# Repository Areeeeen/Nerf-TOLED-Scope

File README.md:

# Nerf-TOLED-Scope
A nerf rail attachment for a 1.51 inch transparent OLED based aiming scope.

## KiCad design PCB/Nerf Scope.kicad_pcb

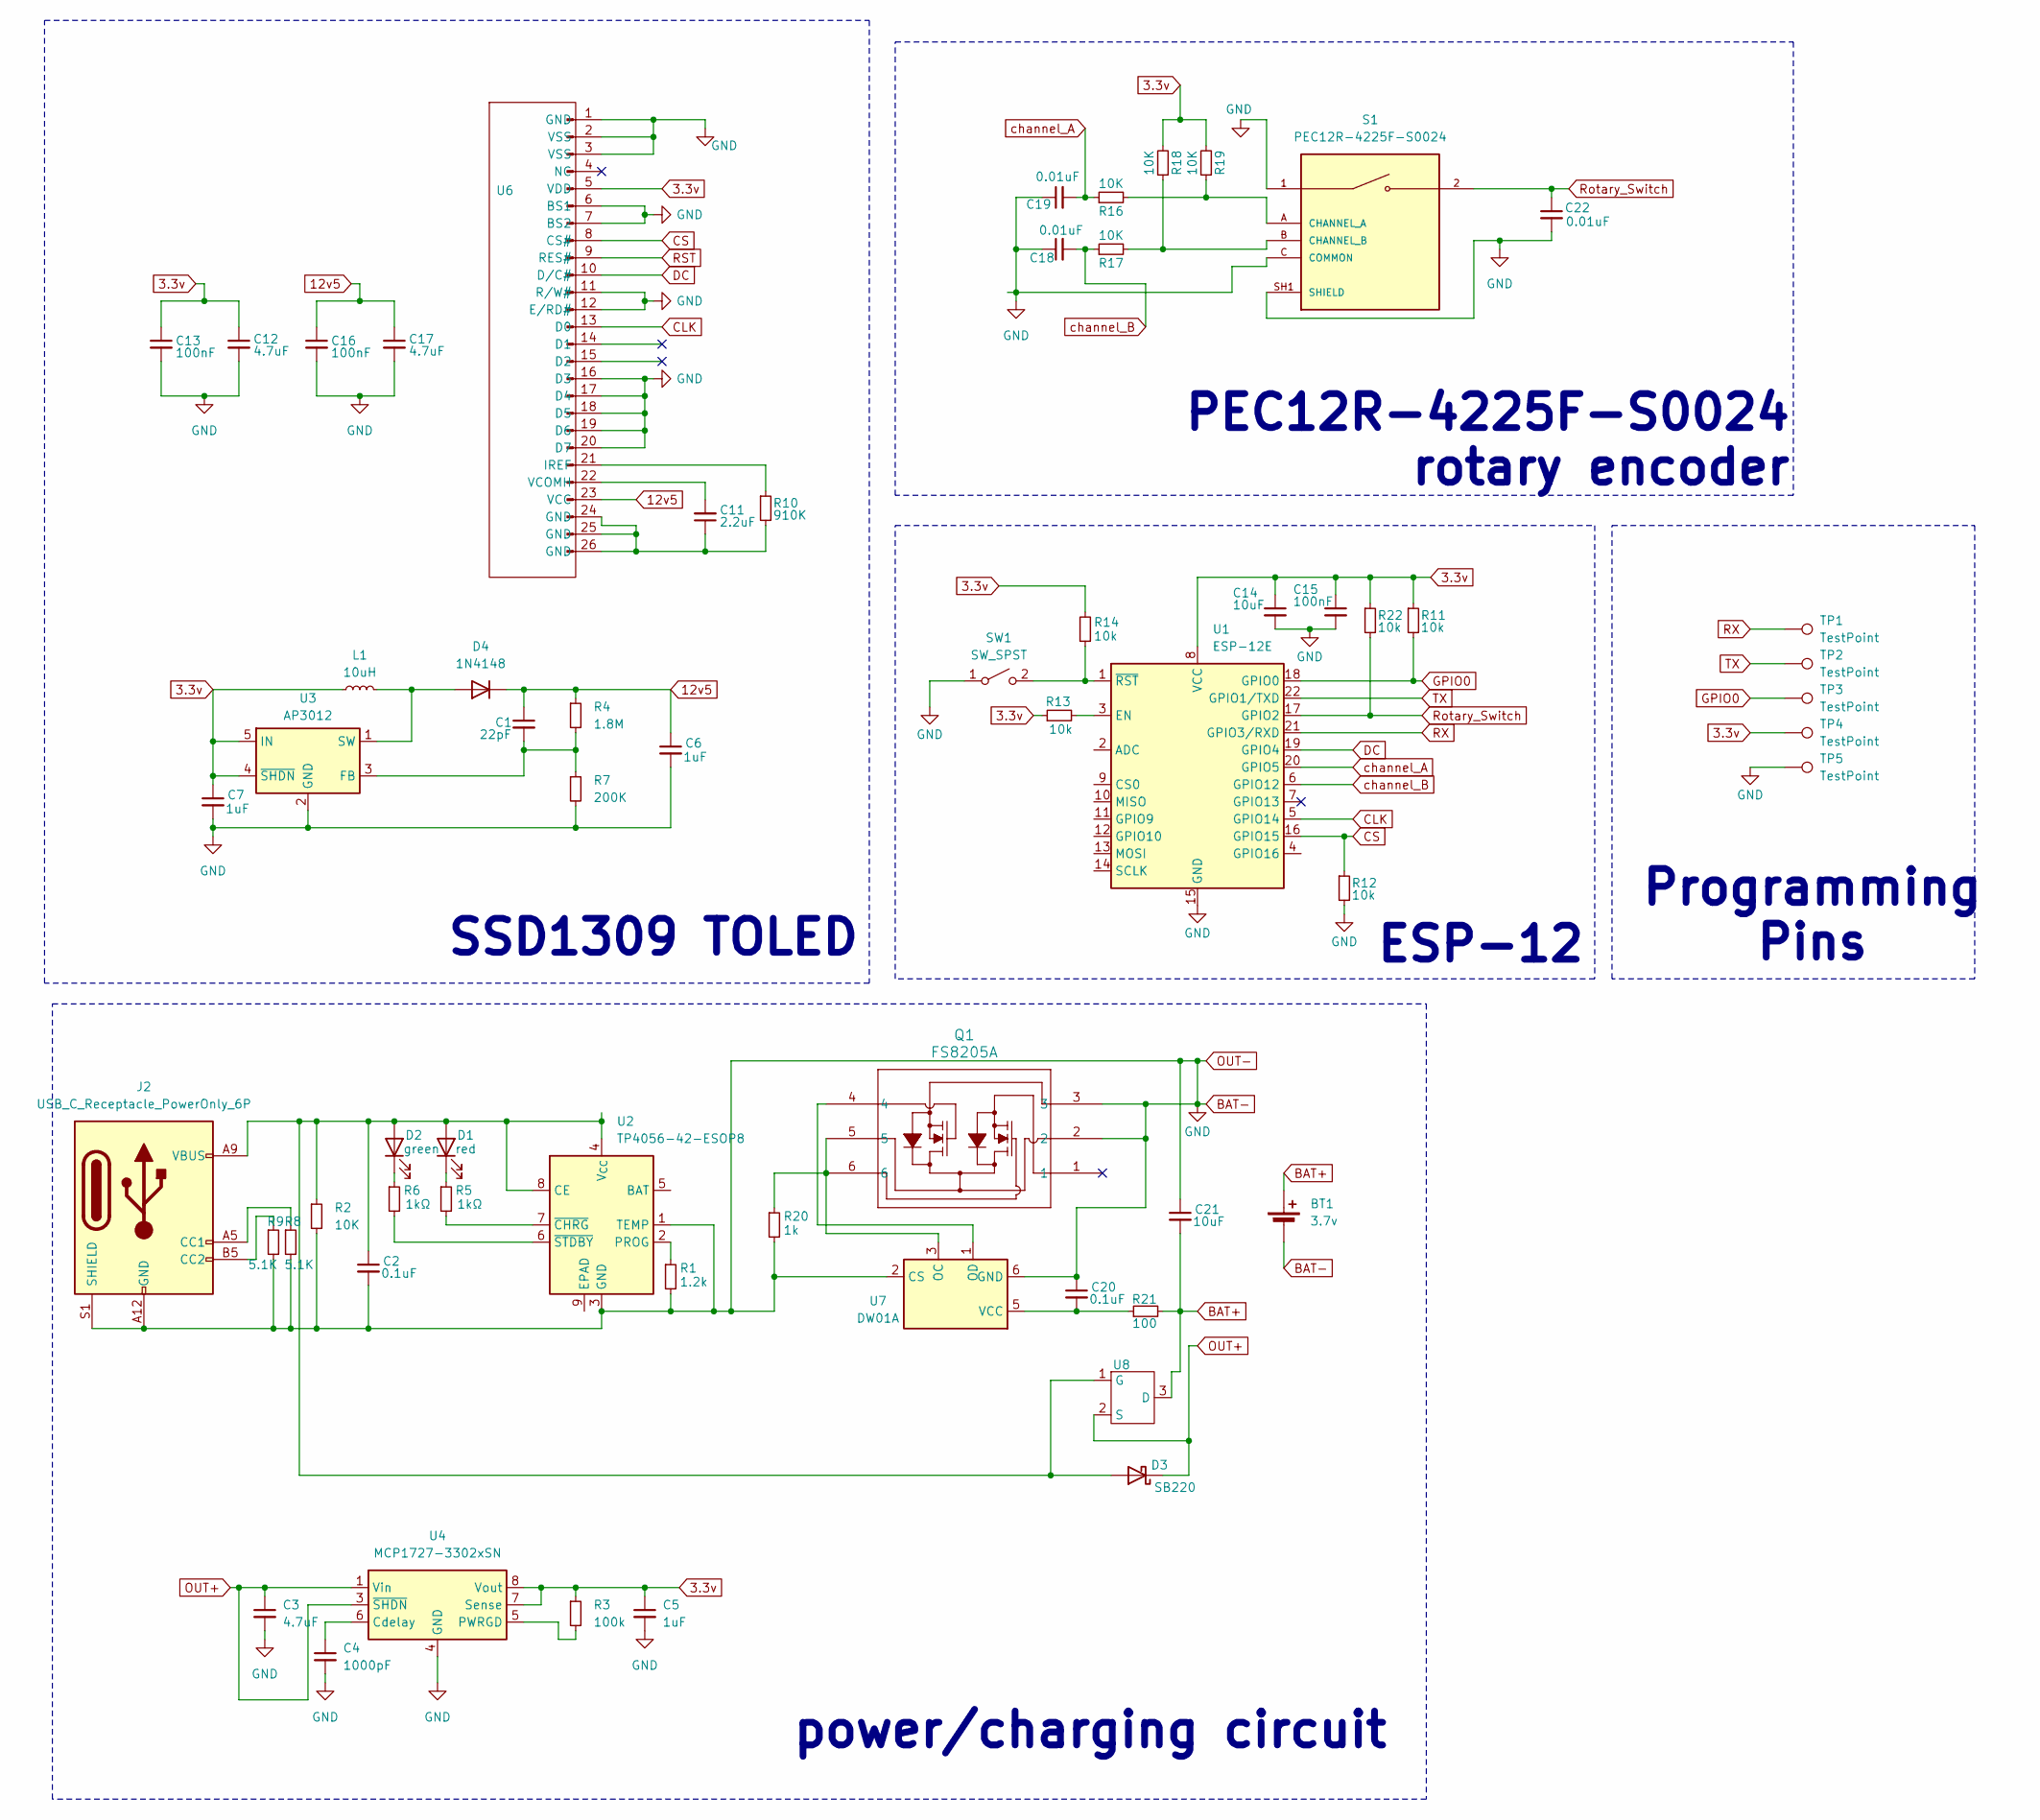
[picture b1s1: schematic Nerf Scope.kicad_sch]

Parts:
BT1: 3.7v; PinHeader_1x02_P2.54mm_Vertical
C1: 22pF; C_0603_1608Metric_Pad1.08x0.95mm_HandSolder
C2, C20: 0.1uF; C_0603_1608Metric_Pad1.08x0.95mm_HandSolder
C3, C12, C17: 4.7uF; C_0603_1608Metric_Pad1.08x0.95mm_HandSolder
C4: 1000pF; C_0603_1608Metric_Pad1.08x0.95mm_HandSolder
C5, C6, C7: 1uF; C_0603_1608Metric_Pad1.08x0.95mm_HandSolder
C11: 2.2uF; C_0603_1608Metric_Pad1.08x0.95mm_HandSolder
C13, C15, C16: 100nF; C_0603_1608Metric_Pad1.08x0.95mm_HandSolder
C14, C21: 10uF; C_0603_1608Metric_Pad1.08x0.95mm_HandSolder
C18, C19, C22: 0.01uF; C_0603_1608Metric_Pad1.08x0.95mm_HandSolder
D1: red; LED_0805_2012Metric_Pad1.15x1.40mm_HandSolder
D2: green; LED_0805_2012Metric_Pad1.15x1.40mm_HandSolder
D3: SB220; D_DO-15_P10.16mm_Horizontal
D4: 1N4148; D_DO-35_SOD27_P7.62mm_Horizontal
J2: USB_C_Receptacle_PowerOnly_6P; USB_C_Receptacle_GCT_USB4125-xx-x-0190_6P_TopMnt_Horizontal
L1: 10uH; Murata_45103C
Q1: FS8205A; SOT-23-6
R1: 1.2k; R_0603_1608Metric_Pad0.98x0.95mm_HandSolder
R2, R16, R17, R18, R19: 10K; R_0603_1608Metric_Pad0.98x0.95mm_HandSolder
R3: 100k; R_0603_1608Metric_Pad0.98x0.95mm_HandSolder
R4: 1.8M; R_0603_1608Metric_Pad0.98x0.95mm_HandSolder
R5, R6: 1kΩ; R_0603_1608Metric_Pad0.98x0.95mm_HandSolder
R7: 200K; R_0603_1608Metric_Pad0.98x0.95mm_HandSolder
R8, R9: 5.1K; R_0603_1608Metric_Pad0.98x0.95mm_HandSolder
R10: 910K; R_0603_1608Metric_Pad0.98x0.95mm_HandSolder
R11, R12, R13, R14, R22: 10k; R_0603_1608Metric_Pad0.98x0.95mm_HandSolder
R20: 1k; R_0603_1608Metric_Pad0.98x0.95mm_HandSolder
R21: 100; R_0603_1608Metric_Pad0.98x0.95mm_HandSolder
S1: PEC12R-4225F-S0024; PARTREV 07/21
SW1: SW_SPST; Untitled
TP1, TP2, TP3, TP4, TP5: TestPoint; Untitled_1
U1: ESP-12E
U2: TP4056-42-ESOP8; SOIC-8-1EP_3.9x4.9mm_P1.27mm_EP2.41x3.3mm_ThermalVias
U3: AP3012; SOT-23-5
U4: MCP1727-3302xSN; SOIC-8_3.9x4.9mm_P1.27mm
U6: Molex_502244-2430_1x24-1MP_P0.5mm_Horizontal
U7: DW01A; SOT-23-6
U8: SOT23-3_PO132

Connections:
3.3v: C5.1, C7.1, C12.1, C13.1, C14.1, C15.1, L1.1, R3.1, R11.1, R13.1, R14.2, R18.2, R19.2, R22.1, TP4.1, U1.8 (VCC), U3.4 (~SHDN), U3.5 (IN), U4.7 (Sense), U4.8 (Vout), U6.5 (VDD)
12v5: C1.1, C6.1, C16.1, C17.1, D4.1 (K), R4.1, U6.23 (VCC)
BAT+: BT1.1 (+), C21.2, R21.2, U8.3 (D)
BAT-: BT1.2 (-), C2.2, C3.2, C4.2, C5.2, C6.2, C7.2, C12.2, C13.2, C14.2, C15.2, C16.2, C17.2, C18.1, C19.1, C20.1, C21.1, C22.2, J2.A12 (GND), J2.B12 (GND), J2.S1 (SHIELD), Q1.2, Q1.3, R1.2, R2.2, R7.2, R8.2, R9.2, R12.2, R20.2, S1.1, S1.C (COMMON), S1.SH1 (SHIELD), S1.SH2 (SHIELD), SW1.1 (A), TP5.1, U1.15 (GND), U2.1 (TEMP), U2.3 (GND), U3.2 (GND), U4.4 (GND), U6.1 (GND), U6.2 (VSS), U6.3 (VSS), U6.6 (BS1), U6.7 (BS2), U6.11 (R/W#), U6.12 (E/RD#), U6.16 (D3), U6.17 (D4), U6.18 (D5), U6.19 (D6), U6.20 (D7), U7.2 (CS), U7.6 (GND)
CLK: U1.5 (GPIO14), U6.13 (D0)
CS: R12.1, U1.16 (GPIO15), U6.8 (CS#)
DC: U1.19 (GPIO4), U6.10 (D/C#)
GPIO0: R11.2, TP3.1, U1.18 (GPIO0)
unnamed: C11.1, R10.2, U6.24 (GND), U6.25 (GND), U6.26 (GND)
unnamed: C2.1, D1.2 (A), D2.2 (A), D3.2 (A), J2.A9 (VBUS), J2.B9 (VBUS), R2.1, U2.4 (V_{CC}), U2.8 (CE), U8.1 (G)
unnamed: D1.1 (K), R5.1
unnamed: D2.1 (K), R6.1
unnamed: D4.2 (A), L1.2, U3.1 (SW)
unnamed: J2.A5 (CC1), R8.1
unnamed: J2.B5 (CC2), R9.1
unnamed: R16.2, R19.1, S1.A (CHANNEL_A)
unnamed: R17.2, R18.1, S1.B (CHANNEL_B)
unnamed: R14.1, SW1.2 (B), U1.1 (~RST)
unnamed: R13.2, U1.3 (EN)
unnamed: R1.1, U2.2 (PROG)
unnamed: R5.2, U2.7 (~CHRG)
unnamed: R6.2, U2.6 (~STDBY)
unnamed: C1.2, R4.2, R7.1, U3.3 (FB)
unnamed: C4.1, U4.6 (Cdelay)
unnamed: R3.2, U4.5 (PWRGD)
unnamed: R10.1, U6.21 (IREF)
unnamed: C11.2, U6.22 (VCOMH)
unnamed: Q1.5, Q1.6, R20.1, U7.3 (OC)
unnamed: Q1.4, U7.1 (OD)
unnamed: C20.2, R21.1, U7.5 (VCC)
OUT+: C3.1, D3.1 (K), U4.1 (Vin), U4.2 (Vin), U4.3 (~SHDN), U8.2 (S)
RST: U6.9 (RES#)
RX: TP1.1, U1.21 (GPIO3/RXD)
Rotary_Switch: C22.1, R22.2, S1.2, U1.17 (GPIO2)
TX: TP2.1, U1.22 (GPIO1/TXD)
channel_A: C19.2, R16.1, U1.20 (GPIO5)
channel_B: C18.2, R17.1, U1.6 (GPIO12)

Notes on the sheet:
power/charging circuit
SSD1309 TOLED
ESP-12
Programming Pins
PEC12R-4225F-S0024 rotary encoder

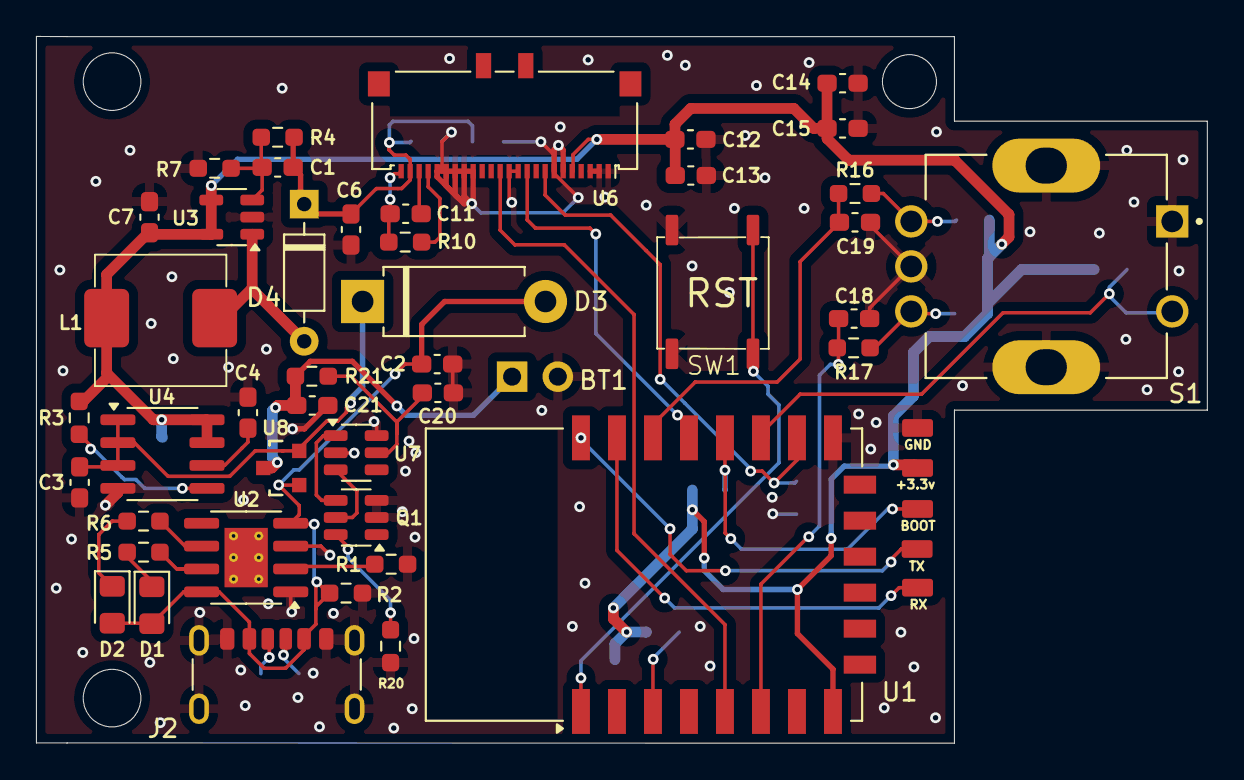
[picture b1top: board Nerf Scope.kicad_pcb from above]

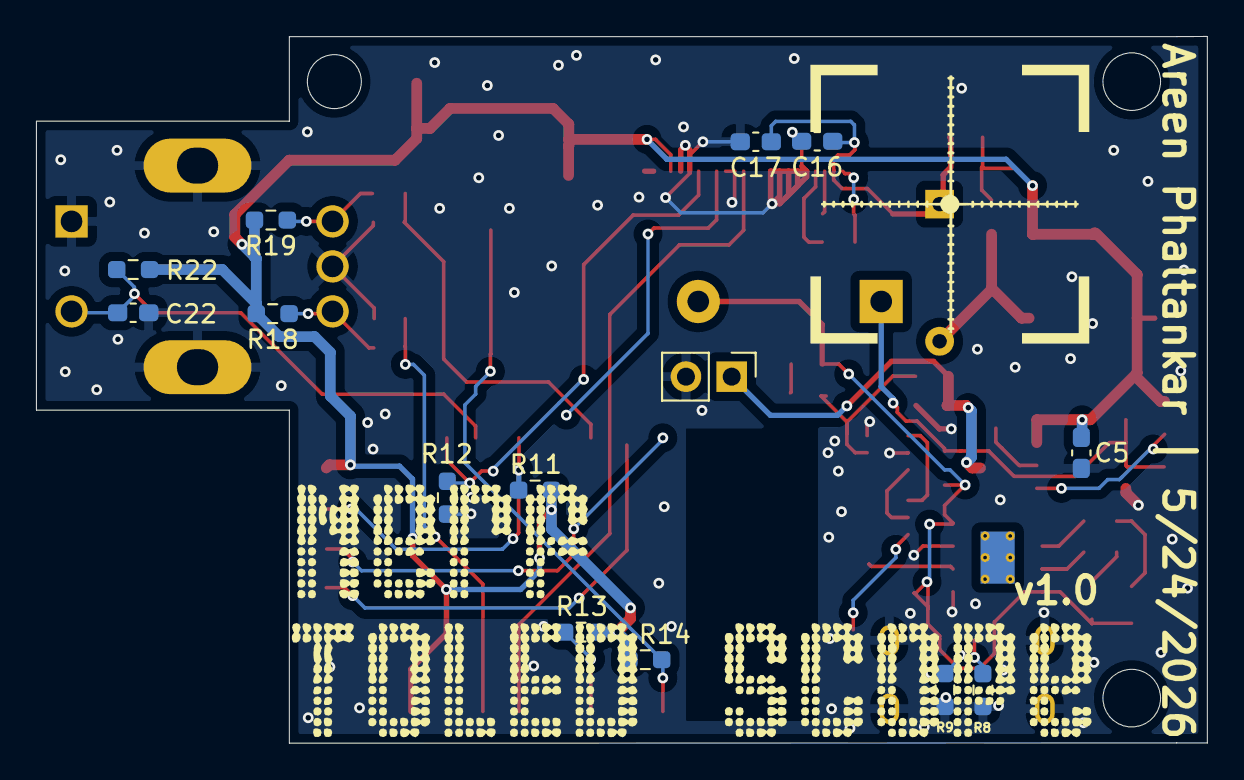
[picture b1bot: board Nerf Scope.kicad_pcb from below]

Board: 2 copper layers, 65.0 x 39.3 mm, 62 parts (14 on the bottom side), 36 nets.

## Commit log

2026-05-26 Uploaded KiCAD PCB design files
2026-06-09 Add images to README for visual reference
    Added images to enhance the README content.
2026-06-09 KiCAD project file (v1.0)
2026-06-09 Add README.md for PCB project files
2026-06-09 Create README.md
    PCB files
2026-06-09 Rename PCB/Nerf Scope.kicad_pcb to PCB/v1.0/Nerf Scope.kicad_pcb
2026-06-09 Add PCB project file for Nerf Scope version 1.0
2026-06-09 Update Nerf Scope schematic file path
